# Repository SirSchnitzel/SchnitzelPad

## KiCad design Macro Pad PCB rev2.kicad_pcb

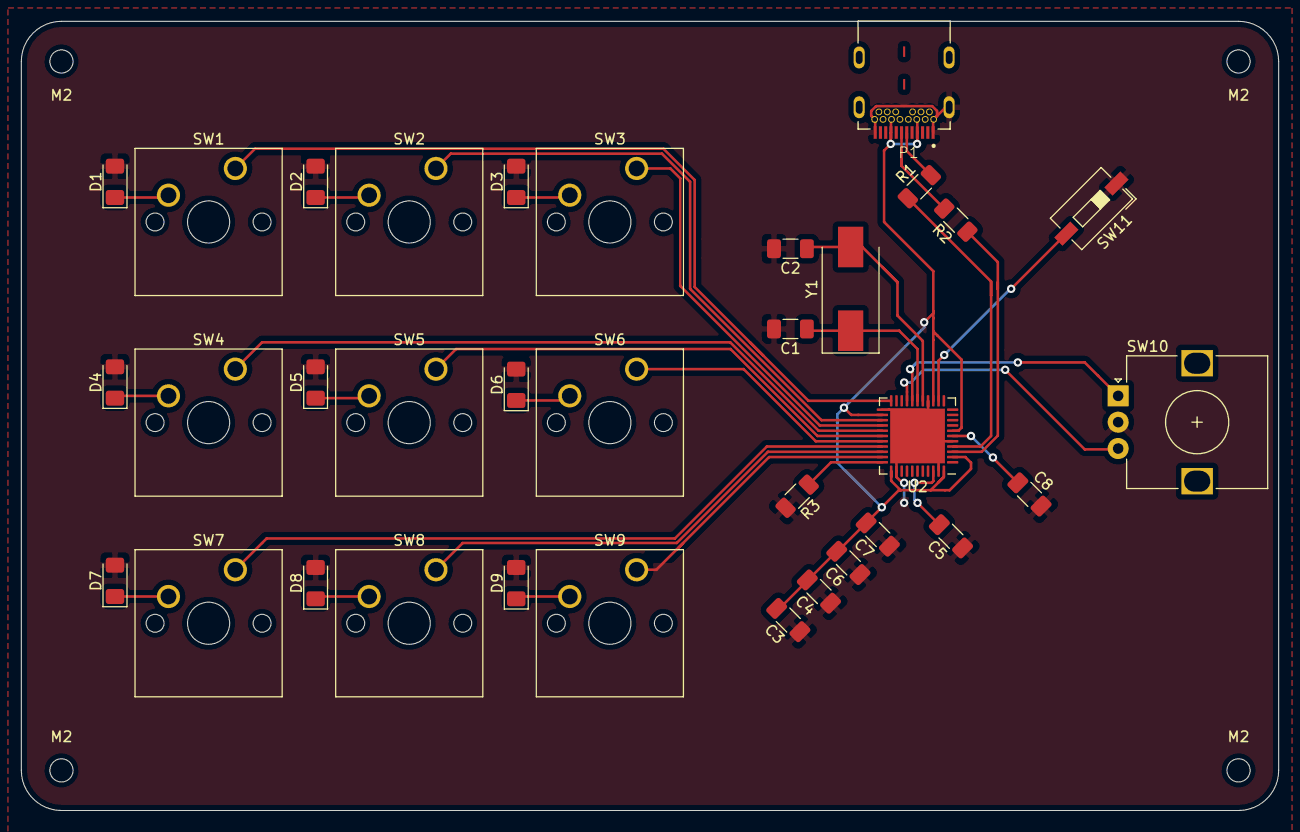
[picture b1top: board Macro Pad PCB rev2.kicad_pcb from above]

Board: 2 copper layers, 119.4 x 74.9 mm, 38 parts (0 on the bottom side), 32 nets.

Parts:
C1, C2: 10 pF; C_1206_3216Metric_Pad1.33x1.80mm_HandSolder
C3, C4, C5, C6: 0.1uF; C_1206_3216Metric_Pad1.33x1.80mm_HandSolder
C7, C8: 1uF; C_1206_3216Metric_Pad1.33x1.80mm_HandSolder
D1, D2, D3, D4, D5, D6, D7, D8, D9: DIODE; D_1206_3216Metric_Pad1.42x1.75mm_HandSolder
M2, M2 , M2#2, M2#3: MountingHole_2.2mm_M2
P1: USB_C_Plug_USB2.0; BELFUSE_SS-52400-002
R1, R2: 22; R_1206_3216Metric_Pad1.30x1.75mm_HandSolder
R3: 1k; R_1206_3216Metric_Pad1.30x1.75mm_HandSolder
SW1, SW2, SW3, SW4, SW5, SW6, SW7, SW8, SW9: SW_Push; SW_Cherry_MX_1.00u_PCB
SW10: Rotary_Encoder; RotaryEncoder_Alps_EC12E_Vertical_H20mm
SW11: SW_Push; SW_DIP_SPSTx01_Slide_6.7x4.1mm_W6.73mm_P2.54mm_LowProfile_J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
U2: ATmega32U4-MU; QFN-44-1EP_7x7mm_P0.5mm_EP5.2x5.2mm
Y1: 16MHz; Crystal_SMD_FOX_FE-2Pin_7.5x5.0mm_HandSoldering

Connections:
GND: C1.2, C2.2, C3.1, C4.1, C5.1, C6.1, C7.1, C8.2, D1.2, D2.2, D3.2, D4.2, D5.2, D6.2, D7.2, D8.2, D9.2, P1.A1, P1.A12, P1.B1, P1.B12, P1.S1, R3.2, SW10.C, SW11.1, U2.5, U2.15, U2.23, U2.35, U2.43, U2.45
unnamed: C1.1, U2.17, Y1.1
unnamed: C2.1, U2.16, Y1.2
unnamed: C3.2, C4.2, C6.2, C7.2, P1.A4, P1.A9, P1.B4, P1.B9, U2.2, U2.7, U2.14, U2.24, U2.34, U2.44
unnamed: C5.2, U2.42
unnamed: C8.1, U2.6
unnamed: D1.1, SW1.2
unnamed: D2.1, SW2.2
unnamed: D3.1, SW3.2
unnamed: D4.1, SW4.2
unnamed: D5.1, SW5.2
unnamed: D6.1, SW6.2
unnamed: D7.1, SW7.2
unnamed: D8.1, SW8.2
unnamed: D9.1, SW9.2
unnamed: SW11.2, U2.13
unnamed: P1.A6, R1.2
unnamed: P1.A7, R2.2
unnamed: R1.1, U2.4
unnamed: R2.1, U2.3
unnamed: R3.1, U2.33
unnamed: SW1.1, U2.22
unnamed: SW2.1, U2.25
unnamed: SW3.1, U2.26
unnamed: SW4.1, U2.27
unnamed: SW5.1, U2.28
unnamed: SW6.1, U2.29
unnamed: SW7.1, U2.30
unnamed: SW8.1, U2.31
unnamed: SW9.1, U2.32
unnamed: SW10.A, U2.18
unnamed: SW10.B, U2.19
